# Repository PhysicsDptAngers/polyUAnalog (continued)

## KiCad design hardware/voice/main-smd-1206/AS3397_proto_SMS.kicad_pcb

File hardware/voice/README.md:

# Monophonic Synth Based on the AS3397 Chip: The Voice Board

These PCBs allow the generation of *one* analog audio voice using the AS3397 chip, controlled by an RP2040/RP2530 (Raspberry Pi Pico) microcontroller.

## Hardware

We offer three different circuit designs:

- **Main (SMD 1206)**: This is the reference board, designed to be controlled by the *conductor board* along with other voice boards to form a polyphonic synthesizer. It uses relatively large *SMD 1206* (Surface-Mounted) components, which can be soldered by hand with some practice.
  
- **Eurorack (SMD 0603) – WIP**: Designed for use with the *Eurorack version of the conductor board* (work in progress as of March 2025). As with all Eurorack modules, space is limited, so this board uses small **SMD 0603** components. While it can be soldered by hand, it requires some experience and possibly dedicated tools like a binocular magnifier.

- **Mono Through-Hole – WIP**: The simplest version to assemble and arguably the best starting point. This is a *standalone* analog voice module that does *not* require a conductor board to generate sound. Additionaly, the board is large and use trhough-hole component (except for the as3397 chip). It also includes a dedicated *MIDI input socket* and *power circuitry*, allowing you to simply connect a MIDI cable and a *+12V power supply* to get a fully functional monophonic analog synthesizer!

## The AS3397 Chip

The AS3397 chip is manufactured by ALFA RPAR, a Latvian semiconductor manufacturer. It's a modern reissue of the CEM3396, a chip that found its home in iconic synthesizers like the Oberheim Matrix-6. 

[Datasheet AS3397](datasheet/AS3397.pdf)

## Sonic Possibilities of the AS3397

### Voltage-Controlled Oscillators (VCOs)

At the heart of the AS3397's sound generation capabilities are two Digital Controlled Oscillators (DCOs), which offer a range of sonic textures from saw waves to clipped triangles thanks to the wave shaper that allows for dynamic waveform manipulation. Additionally, the module can mix square waveforms from both DCOs.

In a nutshell:
- **Dual VCOs**: Specifically, two DCOs, which means the voltage ramp is created by charging a capacitor with a constant current.
- **Wave Shaping**: Converts the sawtooth waveform of the DCO into triangle, clipped triangle, and variations in between.
- **Comparator**: Utilizes the voltage ramp from the DCO to create square waves that are mixed with the output from the wave shaper.
- **Quad Level Driver**: Chooses whether or not to use the output from the DCO.
- **Balance Control**: Allows adjustment of the balance between VCO A and VCO B.

The VCO is arguably the most complex part of the AS3397 to understand. [Here is a link to a detailed explanation of the VCO's operation, outlining its operating principles, the electronics involved, and the connections to the firmware code](doc/VCO.md).

### External Signal Addition

The AS3397 chip allows for the integration of an external audio signal. This a new feature compared to the CEM3396.

### Voltage-Controlled Filter (VCF)

The VCF is a resonant 4-pole low-pass filter that can quite easily auto-oscillate.

For a comprehensive exploration of the Voltage Controlled Filter (VCF) used in the AS3397, please [visit the detailed documentation page](doc/VCF.md).

### Voltage-Controlled Amplifier (VCA)

The AS3397 features a stereo Voltage Controlled Amplifier, which generates a current that must be converted into a corresponding voltage through a "transimpedance" circuit, typically one utilizing an Operational Amplifier (OpAmp). The stereo part of the VCA is a new addition of the AS3397 that was not present in the CEM3396.

## Driving the AS3397 Chip with an RP2040 (Pi Pico)

The integration of the AS3397 chip with the RP2040 microcontroller, particularly through the Pi Pico board, forms the backbone of our voice module's functionality. 

### Discharge Pulse Generation for DCO

The RP2040 plays a crucial role in generating discharge pulses for the Digital Controlled Oscillator's (DCO) capacitor. This ensures the oscillator's frequency stability and precise pitch control, a testament to the seamless integration between analog sound generation and digital control.

### Managing Control Voltages

To fully harness the capabilities of the AS3397, managing numerous control voltages is imperative. Specifically, the chip requires management of 10 control voltages. While employing a Digital to Analog Converter (DAC) and multiplexers could achieve this, such a setup complicates the assembly and increases the overall cost. Instead, we opted for a more efficient approach, utilizing the RP2040's Pulse Width Modulation (PWM) outputs. These outputs are filtered through a low-pass filter to retain only the DC component, ensuring minimal ripple and response times that are well-suited for audio applications. The cut-off frequency of the filter has been meticulously chosen to balance between reducing ripple and maintaining an appropriate response time.

For an in-depth analysis of filtered PWM, including detailed mathematical and technical discussions, please [visit the dedicated page](doc/PCM_CV.md).

### Dynamic Ramp Voltage Control in DCO

Controlling the ramp voltage amplitude within a DCO presents its challenges. Our not so common approach involves continuously sampling the maximum voltage of the DCO's capacitor ramp using the RP2040's Analog to Digital Converters (ADCs). We then dynamically adjust this value using a digital Proportional-Integral-Derivative (PID) feedback loop, ensuring consistent DCO amplitude across different frequencies and hence the same waveform at the exit of the waveshaper.

### Digital Signal Oscillator (DSO)

The second core of the RP2040 is dedicated to generating an audio signal, functioning as a Digital Signal Oscillator (DSO). This digital audio signal is mixed with the analog signal from the AS3397 before reaching the Voltage-Controlled Filter (VCF), enriching the synthesizer's sonic palette.

### Voltage Level Shifting

Considering the AS3397 chip was designed in the 1980s to operate at +5V, while the RP2040 outputs 3.3V, level shifting is necessary. We've implemented level shifters to convert the 3.3V from the RP2040's PWM outputs to the 5V required by the AS3397, ensuring compatibility without sacrificing signal integrity.

### Control Voltage Scaling

For certain control voltages of the AS3397 that can accept broader ranges, we've employed operational amplifiers (Op-Amps) to scale the 0-3.3V output from the RP2040 to the required range. This approach allows for full utilization of the AS3397's control parameters without introducing unnecessary complexity.

### Power Supply

The power supply requirements (+12V, -5V for the AS3397, and +5V for the Pi Pico) are provided externally, for instance, by the conductor board. The Pi Pico employs its internal buck-boost converter to generate the appropriate operating voltage for the RP2040, streamlining the power management across the module.

### External Information Transfer via I²C

The transfer of information from external sources to the RP2040, which in turn controls the AS3397, is facilitated through the I²C bus emulating the MIDI protocol. This setup enables comprehensive control over various musical aspects, including note management (both 'note on' and 'note off'), velocity, aftertouch, control changes (MIDI CC), among other parameters. To surpass the traditional MIDI protocol's limitation of 127 levels, extended MIDI functionality has been integrated, providing greater nuance and control.

A interesting feature of our system is the automatic addressing of each voice board upon the conductor board's startup. Specifically, a voltage, derived by dividing the 3.3V generated by the conductor board and uniquely distributed to each voice board, is measured by the third ADC of the voice board's RP2040. This process assigns a specific I²C channel to each voice board, enabling precise and individualized control. At initialization, the conductor board scans all the connected I²C ports, thus determining the total polyphony capability of the synthesizer, seamlessly integrating hardware and digital controls.

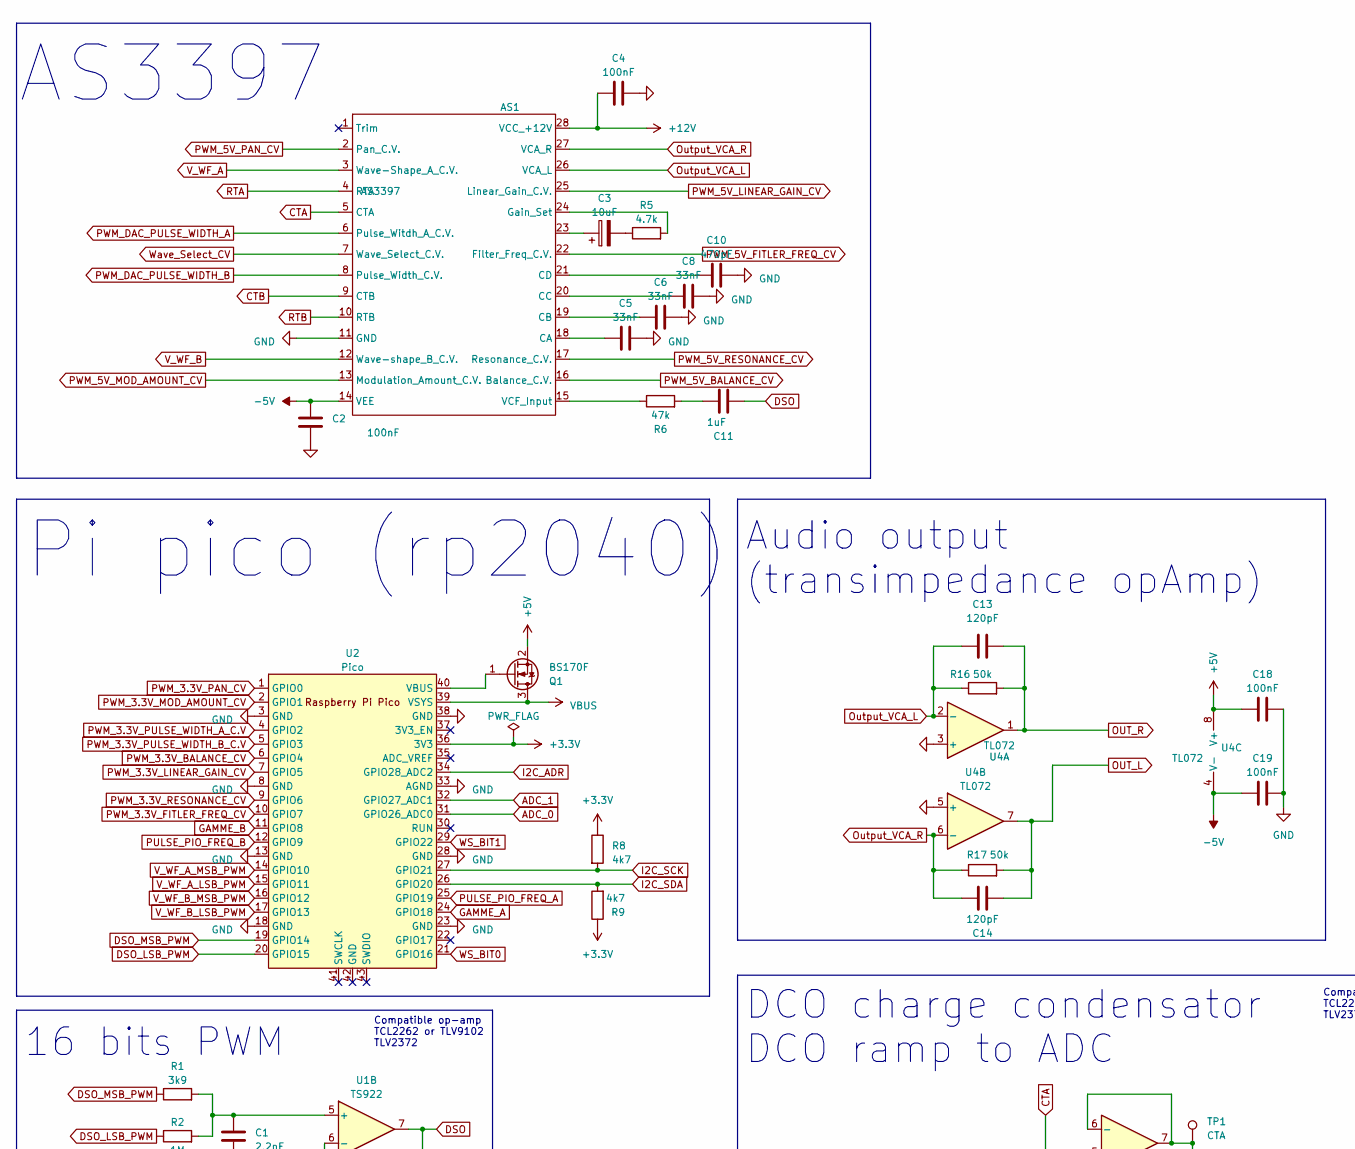
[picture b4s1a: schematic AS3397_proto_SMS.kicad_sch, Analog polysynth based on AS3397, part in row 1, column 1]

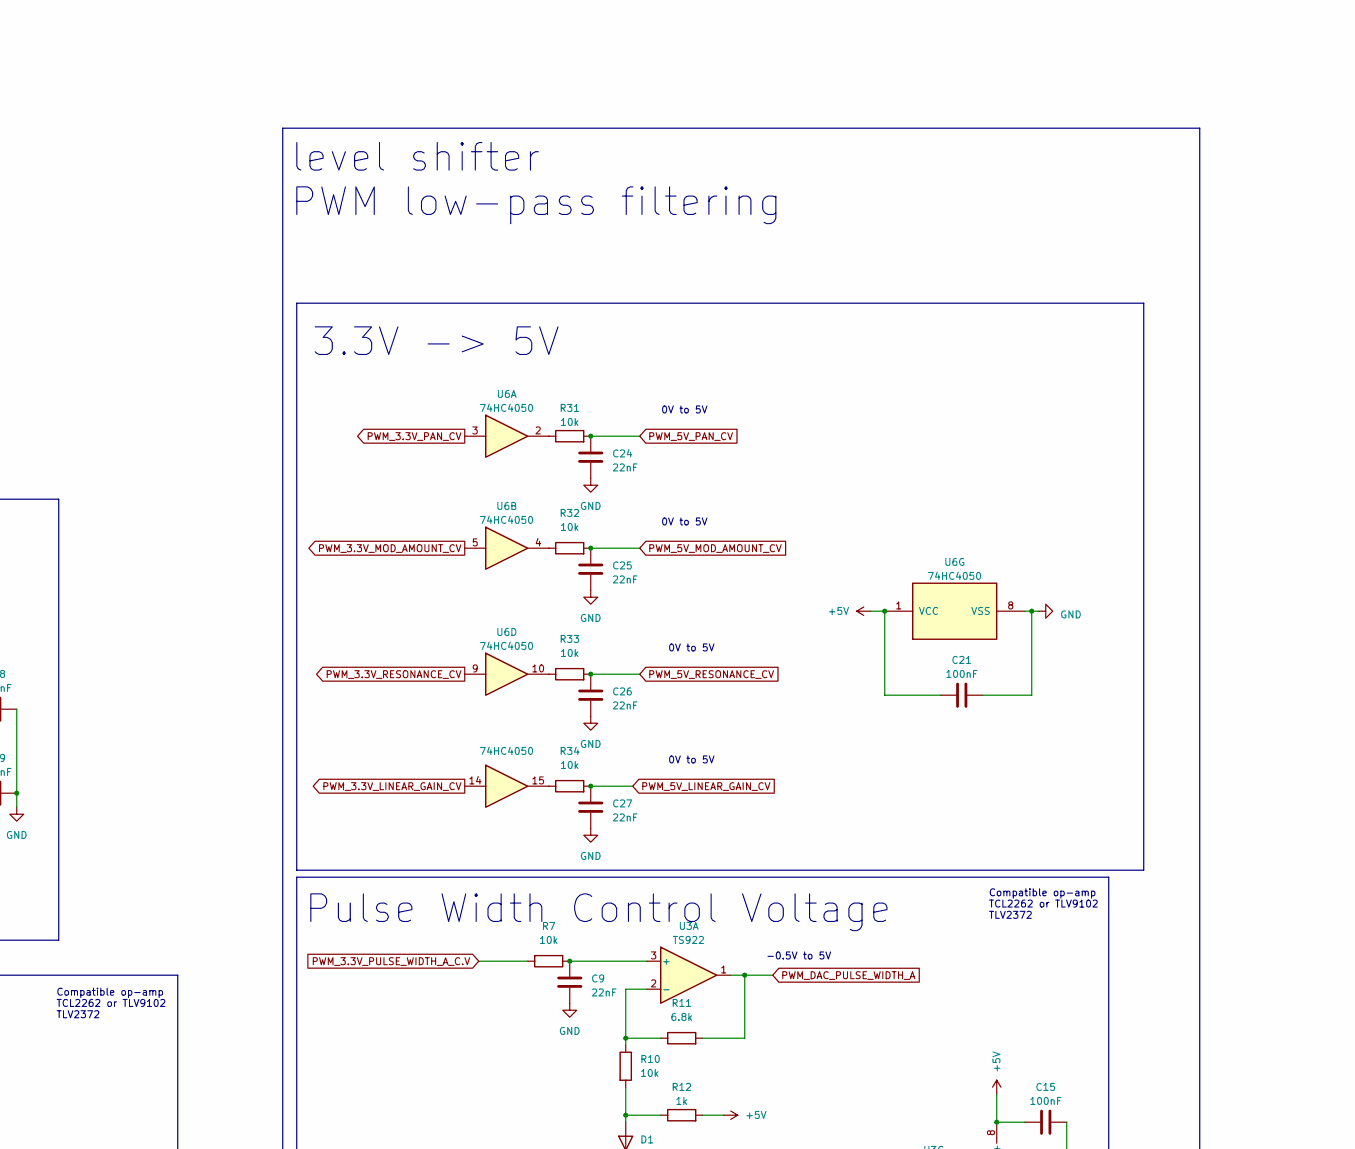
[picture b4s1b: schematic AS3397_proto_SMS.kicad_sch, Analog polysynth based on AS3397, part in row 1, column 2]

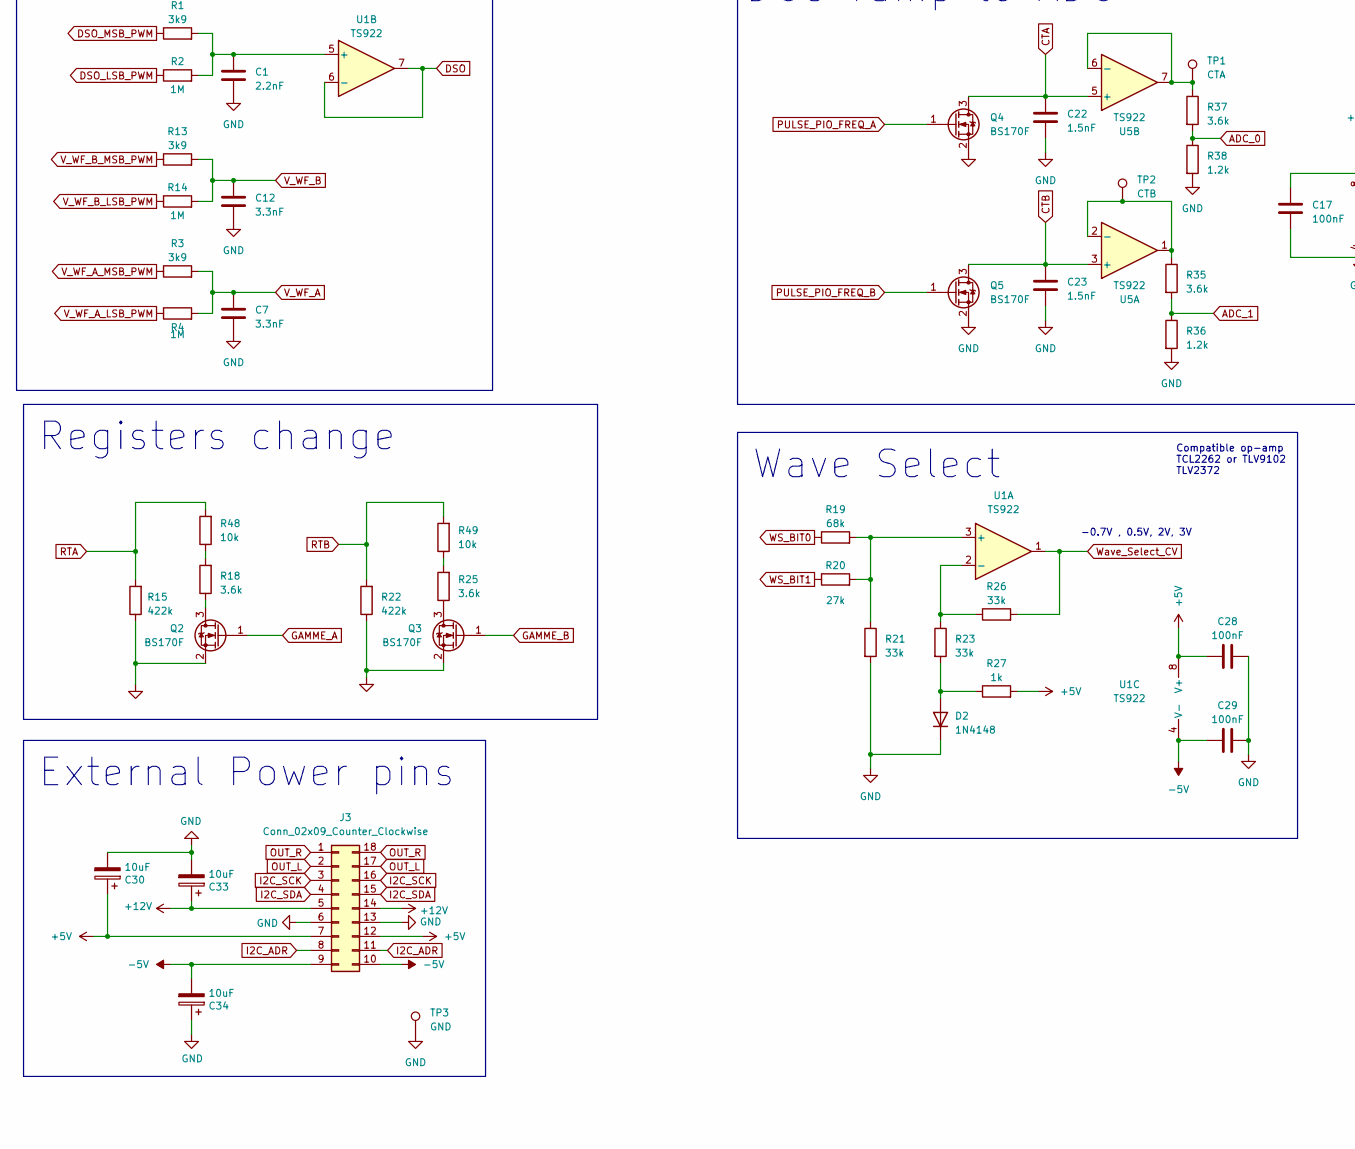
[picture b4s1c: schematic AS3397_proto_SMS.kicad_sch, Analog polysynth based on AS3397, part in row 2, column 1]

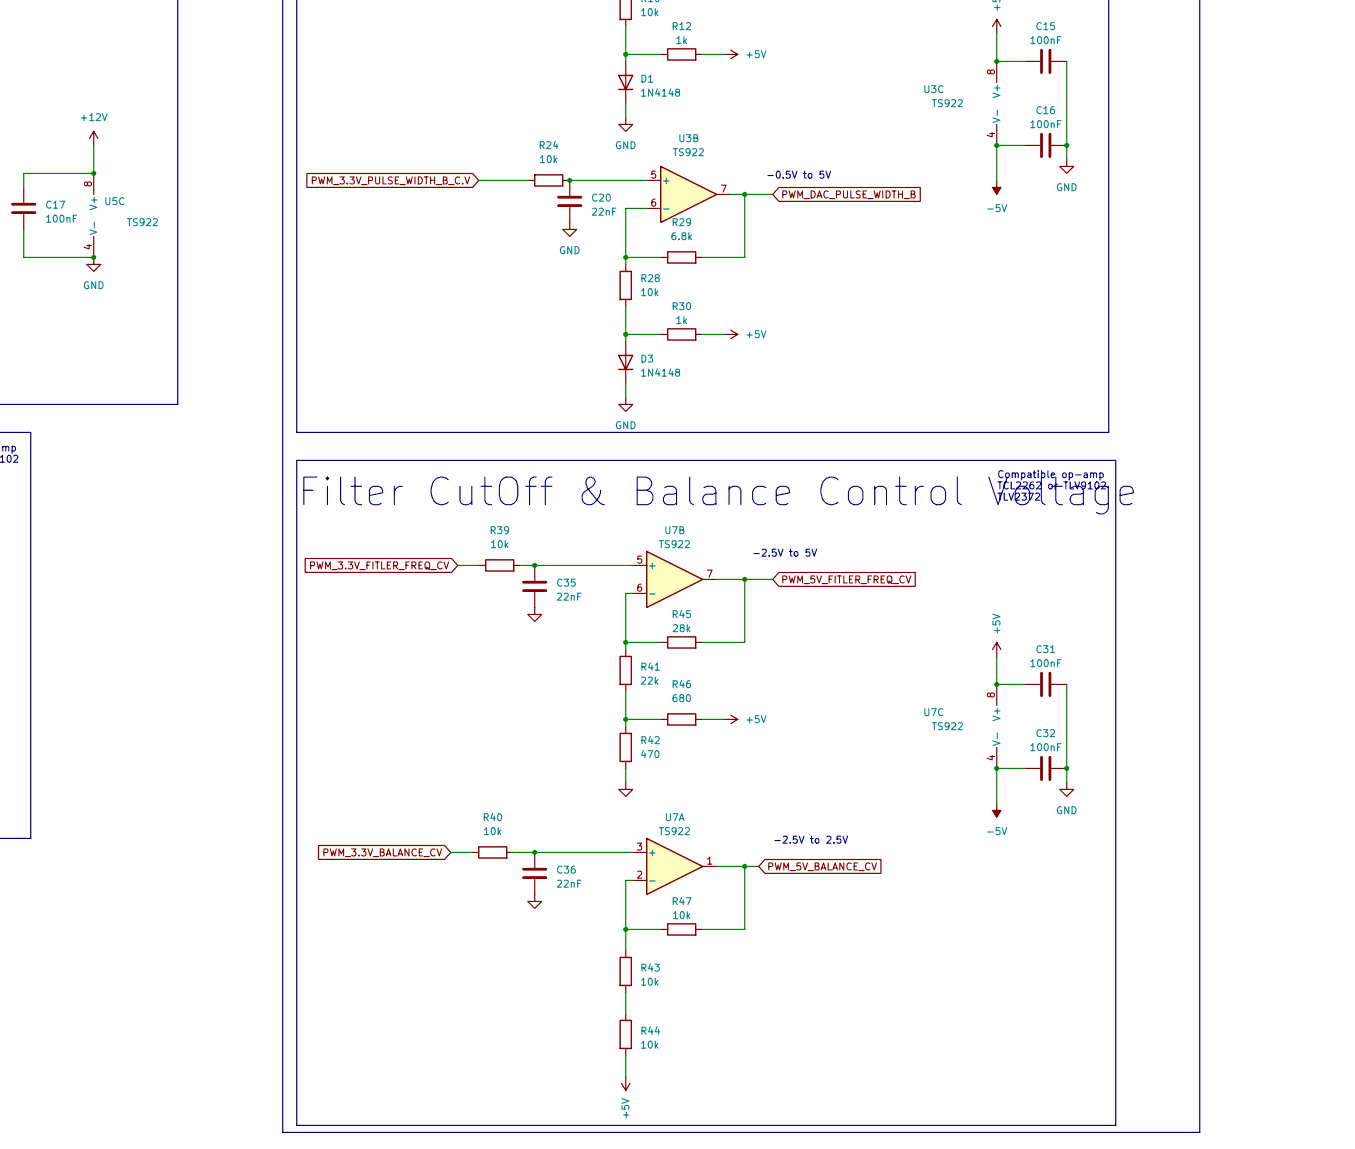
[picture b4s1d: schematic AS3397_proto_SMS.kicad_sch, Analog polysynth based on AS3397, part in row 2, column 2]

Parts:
AS1: AS3397; SOIC-28W_7.5x18.7mm_P1.27mm
C1: 2.2nF; C_1206_3216Metric_Pad1.33x1.80mm_HandSolder
C2, C4, C15, C16, C17, C18, C19, C21, C28, C29, C31, C32: 100nF; C_1206_3216Metric_Pad1.33x1.80mm_HandSolder
C3, C30, C33, C34: 10uF; C_1206_3216Metric_Pad1.33x1.80mm_HandSolder
C5, C6, C8: 33nF; C_1206_3216Metric_Pad1.33x1.80mm_HandSolder
C7, C12: 3.3nF; C_1206_3216Metric_Pad1.33x1.80mm_HandSolder
C9, C20, C24, C25, C26, C27, C35, C36: 22nF; C_1206_3216Metric_Pad1.33x1.80mm_HandSolder
C10: 470pF; C_0805_2012Metric_Pad1.18x1.45mm_HandSolder
C11: 1uF; C_1206_3216Metric_Pad1.33x1.80mm_HandSolder
C13, C14: 120pF; C_0805_2012Metric_Pad1.18x1.45mm_HandSolder
C22, C23: 1.5nF; C_1206_3216Metric_Pad1.33x1.80mm_HandSolder
D1, D2, D3: 1N4148; D_SOD-323
J3: Conn_02x09_Counter_Clockwise; DIP-18_AS
Q1, Q2, Q3, Q4, Q5: BS170F; SOT-23
R1, R3, R13: 3k9; R_1206_3216Metric_Pad1.30x1.75mm_HandSolder
R2, R4, R14: 1M; R_1206_3216Metric_Pad1.30x1.75mm_HandSolder
R5: 4.7k; R_1206_3216Metric_Pad1.30x1.75mm_HandSolder
R6: 47k; R_1206_3216Metric_Pad1.30x1.75mm_HandSolder
R7, R10, R24, R28, R31, R32, R33, R34, R39, R40, R43, R44, R47, R48, R49: 10k; R_1206_3216Metric_Pad1.30x1.75mm_HandSolder
R8, R9: 4k7; R_1206_3216Metric_Pad1.30x1.75mm_HandSolder
R11, R29: 6.8k; R_1206_3216Metric_Pad1.30x1.75mm_HandSolder
R12, R27, R30: 1k; R_1206_3216Metric_Pad1.30x1.75mm_HandSolder
R15, R22: 422k; R_1206_3216Metric_Pad1.30x1.75mm_HandSolder
R16, R17: 50k; R_1206_3216Metric_Pad1.30x1.75mm_HandSolder
R18, R25, R35, R37: 3.6k; R_1206_3216Metric_Pad1.30x1.75mm_HandSolder
R19: 68k; R_1206_3216Metric_Pad1.30x1.75mm_HandSolder
R20: 27k; R_1206_3216Metric_Pad1.30x1.75mm_HandSolder
R21, R23, R26: 33k; R_1206_3216Metric_Pad1.30x1.75mm_HandSolder
R36, R38: 1.2k; R_1206_3216Metric_Pad1.30x1.75mm_HandSolder
R41: 22k; R_1206_3216Metric_Pad1.30x1.75mm_HandSolder
R42: 470; R_1206_3216Metric_Pad1.30x1.75mm_HandSolder
R45: 28k; R_1206_3216Metric_Pad1.30x1.75mm_HandSolder
R46: 680; R_1206_3216Metric_Pad1.30x1.75mm_HandSolder
TP1: CTA; PinHeader_1x01_P2.54mm_Vertical
TP2: CTB; PinHeader_1x01_P2.54mm_Vertical
TP3: GND; PinHeader_1x01_P2.54mm_Vertical
U1, U3, U5, U7: TS922; SOIC-8_3.9x4.9mm_P1.27mm
U2: Pico; RPi_Pico_SMD_TH
U4: TL072; SOIC-8_3.9x4.9mm_P1.27mm
U6: 74HC4050; SOIC-16_3.9x9.9mm_P1.27mm

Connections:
+3.3V: R8.1, R9.1, U2.36 (3V3)
+5V: C15.1, C18.1, C21.1, C28.1, C30.1, C31.1, J3.7, J3.12, Q1.2 (S), R12.2, R27.2, R30.2, R44.2, R46.2, U1.8 (V+), U3.8 (V+), U4.8 (V+), U6.1 (VCC), U7.8 (V+)
+12V: AS1.28 (VCC_+12V), C4.1, C17.2, C33.1, J3.5, J3.14, U5.8 (V+)
-5V: AS1.14 (VEE), C2.1, C16.1, C19.1, C29.1, C32.1, C34.2, J3.9, J3.10, U1.4 (V-), U3.4 (V-), U4.4 (V-), U7.4 (V-)
ADC_0: R37.2, R38.1, U2.31 (GPIO26_ADC0)
ADC_1: R35.2, R36.1, U2.32 (GPIO27_ADC1)
CTA: AS1.5 (CTA), C22.1, Q4.3 (D), U5.5 (+)
CTB: AS1.9 (CTB), C23.1, Q5.3 (D), U5.3 (+)
DSO: C11.2, U1.6 (-), U1.7
DSO_LSB_PWM: R2.1, U2.20 (GPIO15)
DSO_MSB_PWM: R1.1, U2.19 (GPIO14)
GAMME_A: Q2.1 (G), U2.24 (GPIO18)
GAMME_B: Q3.1 (G), U2.11 (GPIO8)
GND: AS1.11 (GND), C1.1, C2.2, C4.2, C5.2, C6.1, C7.1, C8.2, C9.2, C10.2, C12.1, C15.2, C16.2, C17.1, C18.2, C19.2, C20.2, C21.2, C22.2, C23.2, C24.2, C25.2, C26.2, C27.2, C28.2, C29.2, C30.2, C31.2, C32.2, C33.2, C34.1, C35.2, C36.2, D1.1 (K), D2.1 (K), D3.1 (K), J3.6, J3.13, Q2.2 (S), Q3.2 (S), Q4.2 (S), Q5.2 (S), R15.1, R21.2, R22.1, R36.2, R38.2, R42.1, TP3.1, U2.3 (GND), U2.8 (GND), U2.13 (GND), U2.18 (GND), U2.23 (GND), U2.28 (GND), U2.33 (AGND), U2.38 (GND), U4.3 (+), U4.5 (+), U5.4 (V-), U6.8 (VSS)
I2C_ADR: J3.8, J3.11, U2.34 (GPIO28_ADC2)
I2C_SCK: J3.3, J3.16, R8.2, U2.27 (GPIO21)
I2C_SDA: J3.4, J3.15, R9.2, U2.26 (GPIO20)
unnamed: AS1.18 (CA), C5.1
unnamed: AS1.19 (CB), C6.2
unnamed: AS1.20 (CC), C8.1
unnamed: AS1.21 (CD), C10.1
unnamed: AS1.24 (Gain_Set), R5.2
unnamed: AS1.23, C3.1
unnamed: AS1.15 (VCF_Input), R6.1
unnamed: C3.2, R5.1
unnamed: C11.1, R6.2
unnamed: D1.2 (A), R10.2, R12.1
unnamed: D2.2 (A), R23.2, R27.1
unnamed: D3.2 (A), R28.2, R30.1
unnamed: Q1.1 (G), U2.40 (VBUS)
unnamed: Q2.3 (D), R18.1
unnamed: Q3.3 (D), R25.1
unnamed: R18.2, R48.1
unnamed: R25.2, R49.1
unnamed: R31.1, U6.2
unnamed: R32.1, U6.4
unnamed: R33.1, U6.10
unnamed: R34.1, U6.15
unnamed: R41.2, R42.2, R46.1
unnamed: R43.2, R44.1
unnamed: R19.2, R20.2, R21.1, U1.3 (+)
unnamed: R23.1, R26.1, U1.2 (-)
unnamed: C1.2, R1.2, R2.2, U1.5 (+)
unnamed: C9.1, R7.1, U3.3 (+)
unnamed: R10.1, R11.1, U3.2 (-)
unnamed: C20.1, R24.1, U3.5 (+)
unnamed: R28.1, R29.1, U3.6 (-)
unnamed: R35.1, TP2.1, U5.1, U5.2 (-)
unnamed: R37.1, TP1.1, U5.6 (-), U5.7
unnamed: C36.1, R40.2, U7.3 (+)
unnamed: R43.1, R47.1, U7.2 (-)
unnamed: C35.1, R39.2, U7.5 (+)
unnamed: R41.1, R45.1, U7.6 (-)
OUT_L: C14.2, J3.2, J3.17, R17.2, U4.7
OUT_R: C13.2, J3.1, J3.18, R16.2, U4.1
Output_VCA_L: AS1.26 (VCA_L), C13.1, R16.1, U4.2 (-)
Output_VCA_R: AS1.27 (VCA_R), C14.1, R17.1, U4.6 (-)
PULSE_PIO_FREQ_A: Q4.1 (G), U2.25 (GPIO19)
PULSE_PIO_FREQ_B: Q5.1 (G), U2.12 (GPIO9)
PWM_3.3V_BALANCE_CV: R40.1, U2.6 (GPIO4)
PWM_3.3V_FITLER_FREQ_CV: R39.1, U2.10 (GPIO7)
PWM_3.3V_LINEAR_GAIN_CV: U2.7 (GPIO5), U6.14
PWM_3.3V_MOD_AMOUNT_CV: U2.2 (GPIO1), U6.5
PWM_3.3V_PAN_CV: U2.1 (GPIO0), U6.3
PWM_3.3V_PULSE_WIDTH_A_C.V: R7.2, U2.4 (GPIO2)
PWM_3.3V_PULSE_WIDTH_B_C.V: R24.2, U2.5 (GPIO3)
PWM_3.3V_RESONANCE_CV: U2.9 (GPIO6), U6.9
PWM_5V_BALANCE_CV: AS1.16 (Balance_C.V.), R47.2, U7.1
PWM_5V_FITLER_FREQ_CV: AS1.22 (Filter_Freq_C.V.), R45.2, U7.7
PWM_5V_LINEAR_GAIN_CV: AS1.25 (Linear_Gain_C.V.), C27.1, R34.2
PWM_5V_MOD_AMOUNT_CV: AS1.13 (Modulation_Amount_C.V.), C25.1, R32.2
PWM_5V_PAN_CV: AS1.2 (Pan_C.V.), C24.1, R31.2
PWM_5V_RESONANCE_CV: AS1.17 (Resonance_C.V.), C26.1, R33.2
PWM_DAC_PULSE_WIDTH_A: AS1.6 (Pulse_Witdh_A_C.V.), R11.2, U3.1
PWM_DAC_PULSE_WIDTH_B: AS1.8 (Pulse_Width_C.V.), R29.2, U3.7
RTA: AS1.4 (RTA), R15.2, R48.2
RTB: AS1.10 (RTB), R22.2, R49.2
VBUS: Q1.3 (D), U2.39 (VSYS)
V_WF_A: AS1.3 (Wave-Shape_A_C.V.), C7.2, R3.2, R4.2
V_WF_A_LSB_PWM: R4.1, U2.15 (GPIO11)
V_WF_A_MSB_PWM: R3.1, U2.14 (GPIO10)
V_WF_B: AS1.12 (Wave-shape_B_C.V.), C12.2, R13.2, R14.2
V_WF_B_LSB_PWM: R14.1, U2.17 (GPIO13)
V_WF_B_MSB_PWM: R13.1, U2.16 (GPIO12)
WS_BIT0: R19.1, U2.21 (GPIO16)
WS_BIT1: R20.1, U2.29 (GPIO22)
Wave_Select_CV: AS1.7 (Wave_Select_C.V.), R26.2, U1.1

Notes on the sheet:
Compatible op-amp TCL2262 or TLV9102 TLV2372
3.3V -> 5V
Wave Select
16 bits PWM
-0.5V to 5V
level shifter PWM low-pass filtering
0V to 5V
Pi pico (rp2040)
Filter CutOff & Balance Control Voltage
Pulse Width Control Voltage
AS3397
External Power pins
-0.7V , 0.5V, 2V, 3V
Audio output (transimpedance opAmp)
Registers change
DCO charge condensator DCO ramp to ADC
-2.5V to 2.5V
-2.5V to 5V

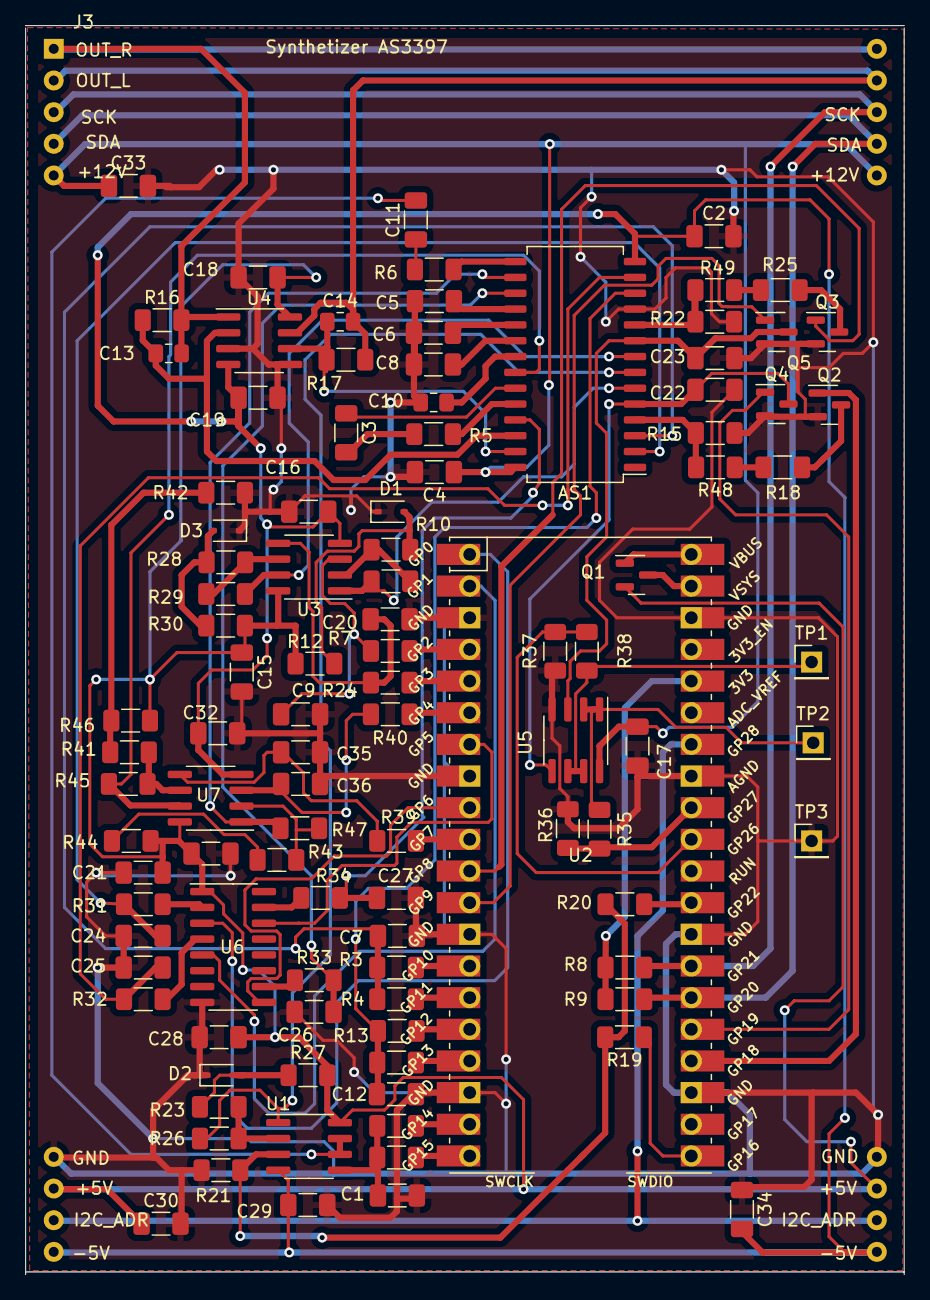
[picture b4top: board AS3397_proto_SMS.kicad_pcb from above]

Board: 2 copper layers, 70.5 x 100.2 mm, 105 parts (0 on the bottom side), 87 nets.

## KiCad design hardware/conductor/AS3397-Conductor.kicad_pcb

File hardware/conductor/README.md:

# Conductor Card

The *Conductor Card* serves as the central hub for the synthesizer, managing communication, power distribution, and analog signal summing. Its architecture is designed to interface external controls with internal voice modules.

## Key Functionalities

### 1. Data I/O & Connectivity

The card manages multiple communication protocols to interface with the outside world:

* **MIDI:** Standard MIDI IN port and an optional MIDI OUT header.
* **I2C**:
	* Dedicated header for optional *"Controllers"* (e.g., a front panel equipped with knobs and sliders for real-time parameter control).
	* Dedicated header for optional *"FX card"*
* **Wireless (UDP):** Support for UDP over Wi-Fi when utilizing a *Raspberry Pi Pico 2 W*.
* **Storage:** Integrated SD card slot for storing and retrieving presets and system data.

### 2. Voice Dispatch & Power Distribution

The Conductor Card serves as the central interface for system data and power management:

* **Power Input:** Features a dedicated input port for the main power rails (*+12V, -12V, +5V*).
* **Power Routing:** Distributes stable power rails from the main input to all connected internal modules and voice cards.
* **Signal Dispatch:** Routes digital control data—including **Note On/Off, MIDI CC, and Clock** signals—to the individual voice cards via the *I2C bus*.

### 3. Analog Signal Processing & Mixing

The card features a dedicated analog summing stage to consolidate the synthesizer's output:

* **Current-to-Voltage Conversion:** Collects the current outputs from the *AS3397-based voice cards* via a Trans-Impedance Amplifier (TIA).
* **FX Integration:** Bi-directional interfacing with an optional FX card (Send/Return or post-summing injection).
* **Final Mix:** Sums the voice signals with the FX return to produce the final audio output.

## Connectors Pinouts

### 1. Voice Connector (J13)
Single row header (1x9).

```text
┌───┬───┬───┬───┬───┬───┬───┬───┬───┐
│ 1 │ 2 │ 3 │ 4 │ 5 │ 6 │ 7 │ 8 │ 9 │
└───┴───┴───┴───┴───┴───┴───┴───┴───┘
  │   │   │   │   │   │   │   │   │
  │   │   │   │   │   │   │   │   └─ -5V
  │   │   │   │   │   │   │   └───  +3.3V (for i2c Address)
  │   │   │   │   │   │   └───── +5V
  │   │   │   │   │   └─────── GND
  │   │   │   │   └───────── +12V
  │   │   │   └─────────── I2C_Voices_SDA
  │   │   └───────────── I2C_Voices_SCL
  │   └─────────────── Audio_Analog_Right
  └───────────────── Audio_Analog_Left

```

### 2. Power Input (J7 - Conn_POWER)

Dual row header (2x10).

```text
       ┌───────────┐
   -5V │ 1       2 │ GND
   GND │ 3       4 │ +5V
   GND │ 5       6 │ +12V
   GND │ 7       8 │ GND
   GND │ 9      10 │ GND
       └───────────┘

```

### 3. I2C Controller (J15)

Single row header (1x4).

```text
  ┌───┬───┬───┬───┐
  │ 1 │ 2 │ 3 │ 4 │
  └───┴───┴───┴───┘
    │   │   │   │
    │   │   │   └─ GND
    │   │   └─── +3.3V
    │   └───── I2C_CTRL_SDA
    └─────── I2C_CTRL_SCL

```

### 4. FX Connector (J9/J10)

Dual row header (2x10).

```text
       ┌───────────┐
  Dry_L│ 1       2 │ I2C_CTRL_SCL
  Wet_L│ 3       4 │ I2C_CTRL_SDA
  Dry_R│ 5       6 │ -5V
  Wet_R│ 7       8 │ +12V
    GND│ 9      10 │ +5V
       └───────────┘

```

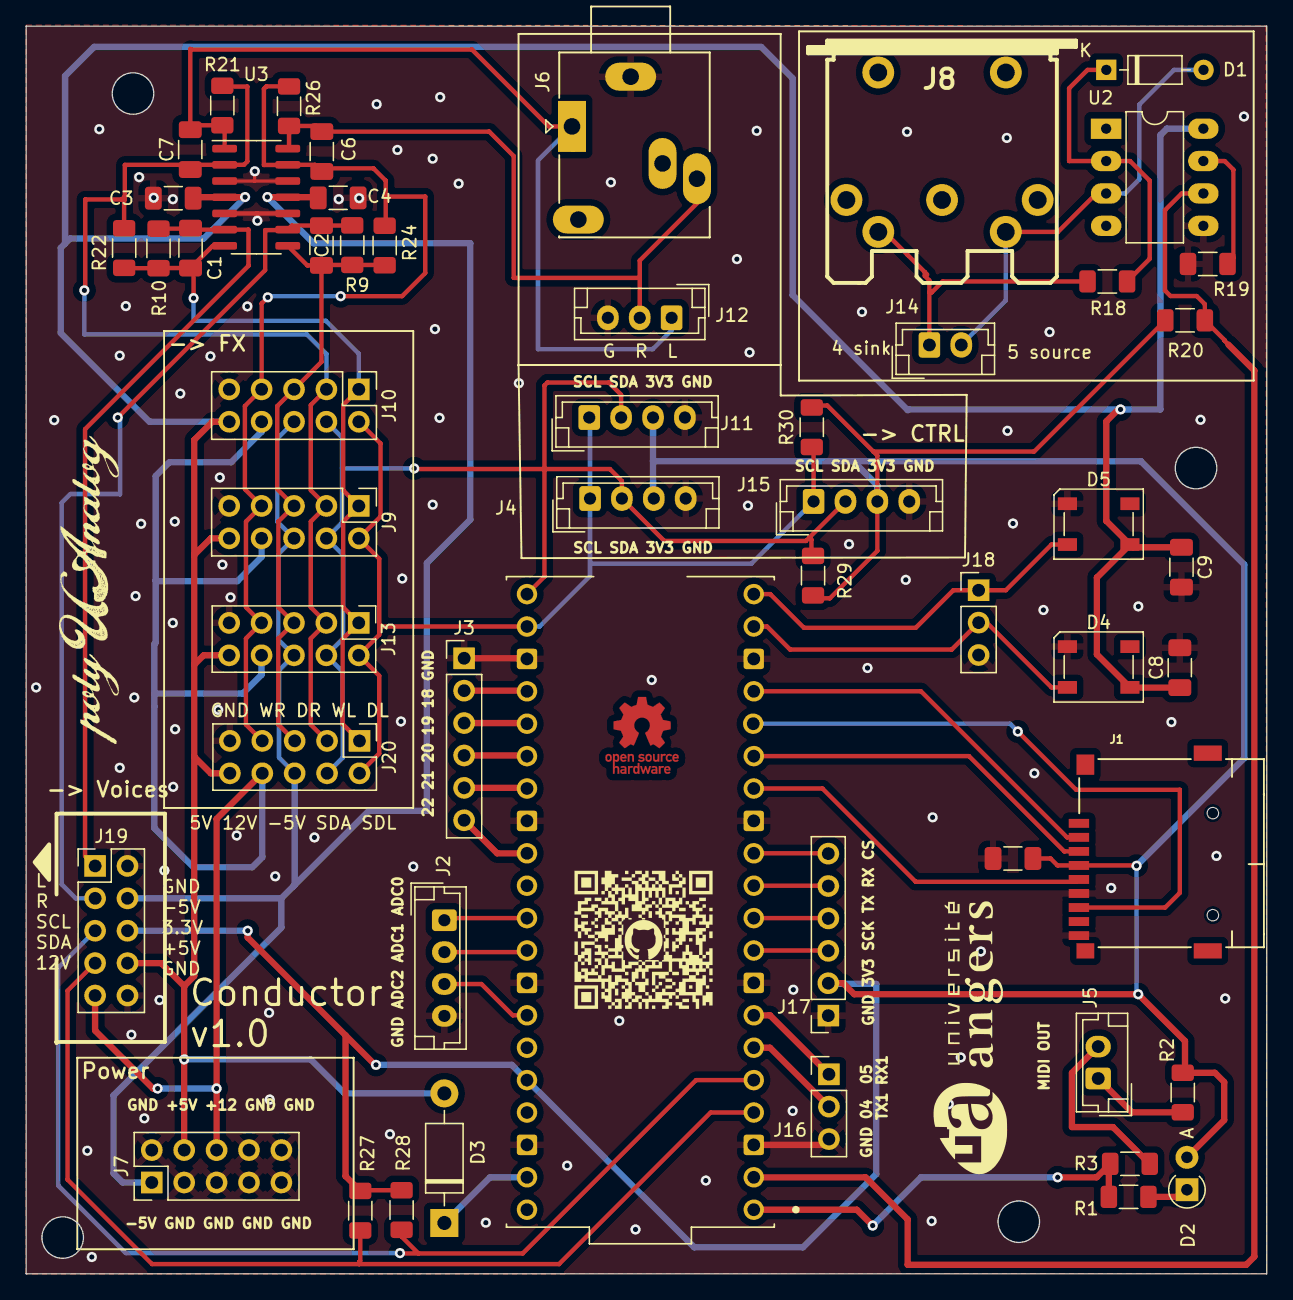
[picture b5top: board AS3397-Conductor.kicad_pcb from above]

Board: 2 copper layers, 97.3 x 97.8 mm, 53 parts (0 on the bottom side), 47 nets.

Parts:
A1: SC0918; MODULE_SC0918
C1, C2, C6, C7: 120pF; C_1206_3216Metric_Pad1.33x1.80mm_HandSolder
C3, C4, C5, C8, C9: 100n; C_1206_3216Metric_Pad1.33x1.80mm_HandSolder
D1: 1N4148; D_DO-35_SOD27_P7.62mm_Horizontal
D2: LED; D_A-405_P2.54mm_Vertical_AnodeUp
D3: 1N5819; D_DO-41_SOD81_P10.16mm_Horizontal
D4, D5: SK6812; LED_SK6812_PLCC4_5.0x5.0mm_P3.2mm
J1: Micro_SD_Card; J_SD_Card-micro_socket_A
J2: ADC_connector; JST_EH_B4B-EH-A_1x04_P2.50mm_Vertical
J3: Conn_01x06_Socket; PinHeader_1x06_P2.54mm_Vertical
J4, J11, J15: I2C controller; JST_EH_B4B-EH-A_1x04_P2.50mm_Vertical
J5, J14: Conn_01x02_Socket; JST_EH_B2B-EH-A_1x02_P2.50mm_Vertical
J6: AudioJack3; Jack_3.5mm_Ledino_KB3SPRS_Horizontal
J7: Conn_POWER; PinHeader_2x05_P2.54mm_Vertical
J8: MIDI IN; MIDI_DIN5
J9: Conn_FX_1; PinHeader_2x05_P2.54mm_Vertical
J10: Conn_FX_2; PinHeader_2x05_P2.54mm_Vertical
J12: Conn_01x03_Socket_AudioOUT; JST_EH_B3B-EH-A_1x03_P2.50mm_Vertical
J13: Conn_FX_3; PinHeader_2x05_P2.54mm_Vertical
J16: Conn_01x06_Socket_SPI; PinSocket_1x06_P2.54mm_Vertical
J17, J18: Conn_01x03_Socket; PinHeader_1x03_P2.54mm_Vertical
J19: Conn_Voice; PinHeader_2x05_P2.54mm_Vertical
J20: Conn_FX_4; PinHeader_2x05_P2.54mm_Vertical
R1: 1K; R_1206_3216Metric_Pad1.30x1.75mm_HandSolder
R2, R3: 51; R_1206_3216Metric_Pad1.30x1.75mm_HandSolder
R9, R10, R22, R24: 10K; R_1206_3216Metric_Pad1.30x1.75mm_HandSolder
R18: 220; R_1206_3216Metric_Pad1.30x1.75mm_HandSolder
R19: 4k7; R_1206_3216Metric_Pad1.30x1.75mm_HandSolder
R20: 470; R_1206_3216Metric_Pad1.30x1.75mm_HandSolder
R21, R26: 5K1; R_1206_3216Metric_Pad1.30x1.75mm_HandSolder
R27, R28, R29, R30: 4K7; R_1206_3216Metric_Pad1.30x1.75mm_HandSolder
U2: 6N138; DIP-8_W7.62mm_LongPads
U3: OPA1679; SOIC-14_3.9x8.7mm_P1.27mm

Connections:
+3.3V: A1.36 (3V3_OUT), C5.2, D2.2 (A), J1.4 (VDD), J4.3, J11.3, J15.3, J16.2, J19.6, R2.1, R20.1, R27.2, R28.1, R29.2, R30.1
+5V: C3.1, C8.1, C9.1, D3.2 (A), D4.3 (VDD), D5.3 (VDD), J7.4, J9.10, J10.10, J13.10, J19.8, J20.10, U2.8 (VCC), U3.4 (V+)
+12V: J7.6, J9.8, J10.8, J13.8, J19.9, J20.8
-5V: C4.1, J7.1, J9.6, J10.6, J13.6, J19.4, J20.6, U3.11 (V-)
ADC0: A1.31 (GP26), J2.1
ADC1: A1.32 (GP27), J2.2
ADC2: A1.34 (GP28), J2.3
Dry_left: C1.2, J9.1, J10.1, J13.1, J20.1, R10.2, R22.1, U3.7
Dry_right: C2.2, J9.5, J10.5, J13.5, J20.5, R9.2, R24.1, U3.8
GND: A1.3 (GND), A1.8 (GND), A1.13 (GND), A1.18 (GND), A1.23 (GND), A1.28 (GND), A1.33 (AGND), A1.38 (GND), C3.2, C4.2, C5.1, C8.2, C9.2, D4.1 (VSS), D5.1 (VSS), J1.6 (VSS), J1.9 (SHIELD), J2.4, J3.1, J4.4, J6.S, J7.2, J7.3, J7.5, J7.7, J7.8, J7.9, J7.10, J9.9, J10.9, J11.4, J12.3, J13.9, J15.4, J16.1, J17.3, J18.3, J19.2, J19.10, J20.9, R19.2, U2.5 (GND), U3.3 (+), U3.5 (+), U3.10 (+), U3.12 (+)
GPIO4: A1.6 (GP4), J17.2
GPIO5: A1.7 (GP5), J17.1
GPIO14: A1.19 (GP14), D4.2 (DIN), J18.2
GPIO15: A1.20 (GP15), D5.2 (DIN), J18.1
GPIO18: A1.24 (GP18), J3.2
GPIO19: A1.25 (GP19), J3.3
GPIO20: A1.26 (GP20), J3.4
GPIO21: A1.27 (GP21), J3.5
GPIO22: A1.29 (GP22), J3.6
I2C_CTRL_SDA: A1.21 (GP16), J4.2, J9.4, J10.4, J11.2, J13.4, J15.2, J20.4, R29.1
I2C_CTRL_SDL: A1.22 (GP17), J4.1, J9.2, J10.2, J11.1, J13.2, J15.1, J20.2, R30.2
I2C_voices_SDA: A1.4 (GP2), J19.7, R27.1
I2C_voices_SDL: A1.5 (GP3), J19.5, R28.2
unnamed: A1.39 (VSYS), D3.1 (K)
unnamed: D1.2 (A), J8.5, J14.2, U2.3 (C2)
unnamed: D1.1 (K), R18.2, U2.2 (C1)
unnamed: D2.1 (K), R1.2
unnamed: J5.1, R2.2
unnamed: J5.2, R3.2
unnamed: J8.4, J14.1, R18.1
unnamed: R19.1, U2.7 (VO1)
Out_left: C7.2, J6.T, J12.1, R21.2, U3.1
Out_right: C6.2, J6.R, J12.2, R26.2, U3.14
RX_MIDI: A1.2 (GP1), R20.2, U2.6 (VO2)
SD_CS: A1.17 (GP13), J1.2 (DAT3/CD)
SD_MISO: A1.16 (GP12), J1.7 (DAT0)
SD_MOSI: A1.15 (GP11), J1.3 (CMD)
SD_SCLK: A1.14 (GP10), J1.5 (CLK)
SPI0_CS: A1.12 (GP9), J16.6
SPI0_RX: A1.11 (GP8), J16.5
SPI0_SCK: A1.9 (GP6), J16.3
SPI0_TX: A1.10 (GP7), J16.4
TX_MIDI: A1.1 (GP0), R1.1, R3.1
Wet_left: C7.1, J9.3, J10.3, J13.3, J20.3, R21.1, R22.2, U3.2 (-)
Wet_right: C6.1, J9.7, J10.7, J13.7, J20.7, R24.2, R26.1, U3.13 (-)
audio_analog_left: C1.1, J19.1, R10.1, U3.6 (-)
audio_analog_right: C2.1, J19.3, R9.1, U3.9 (-)
